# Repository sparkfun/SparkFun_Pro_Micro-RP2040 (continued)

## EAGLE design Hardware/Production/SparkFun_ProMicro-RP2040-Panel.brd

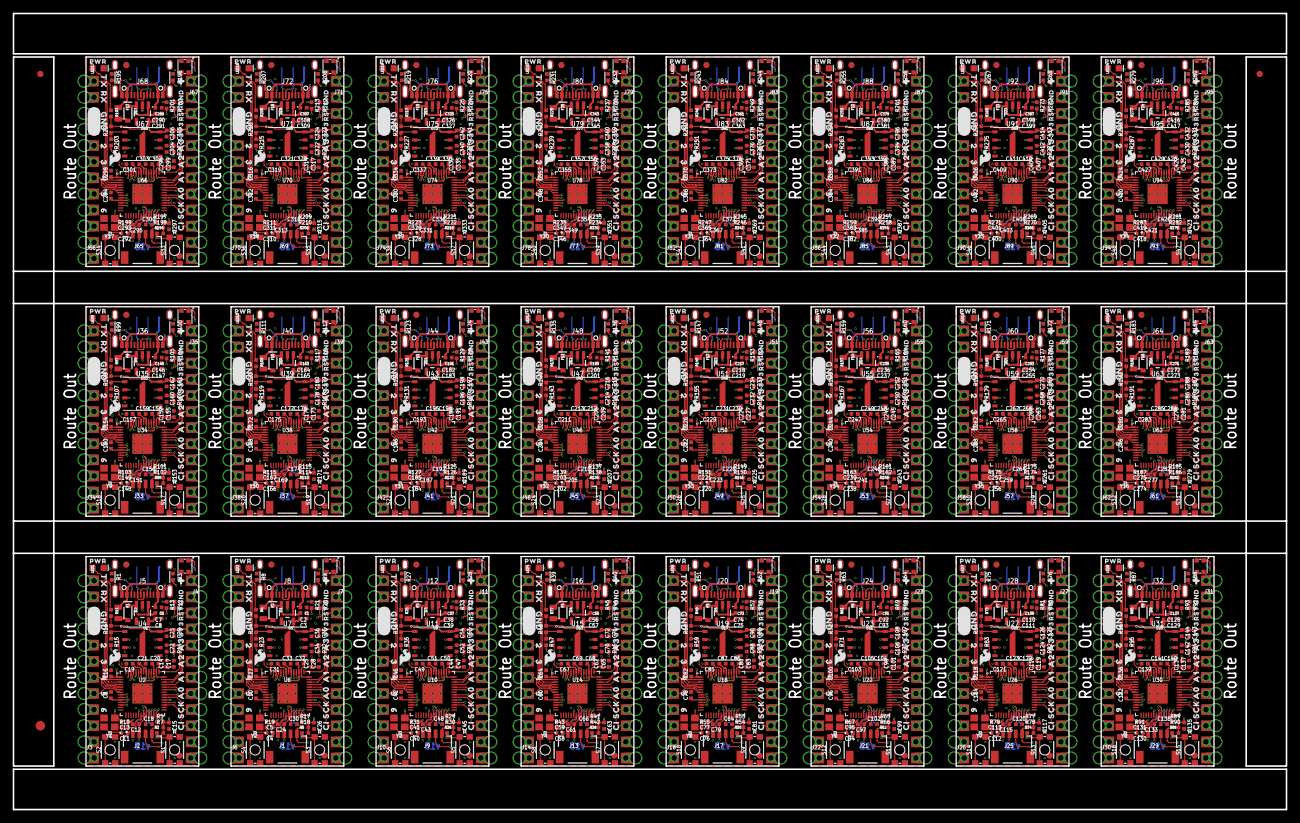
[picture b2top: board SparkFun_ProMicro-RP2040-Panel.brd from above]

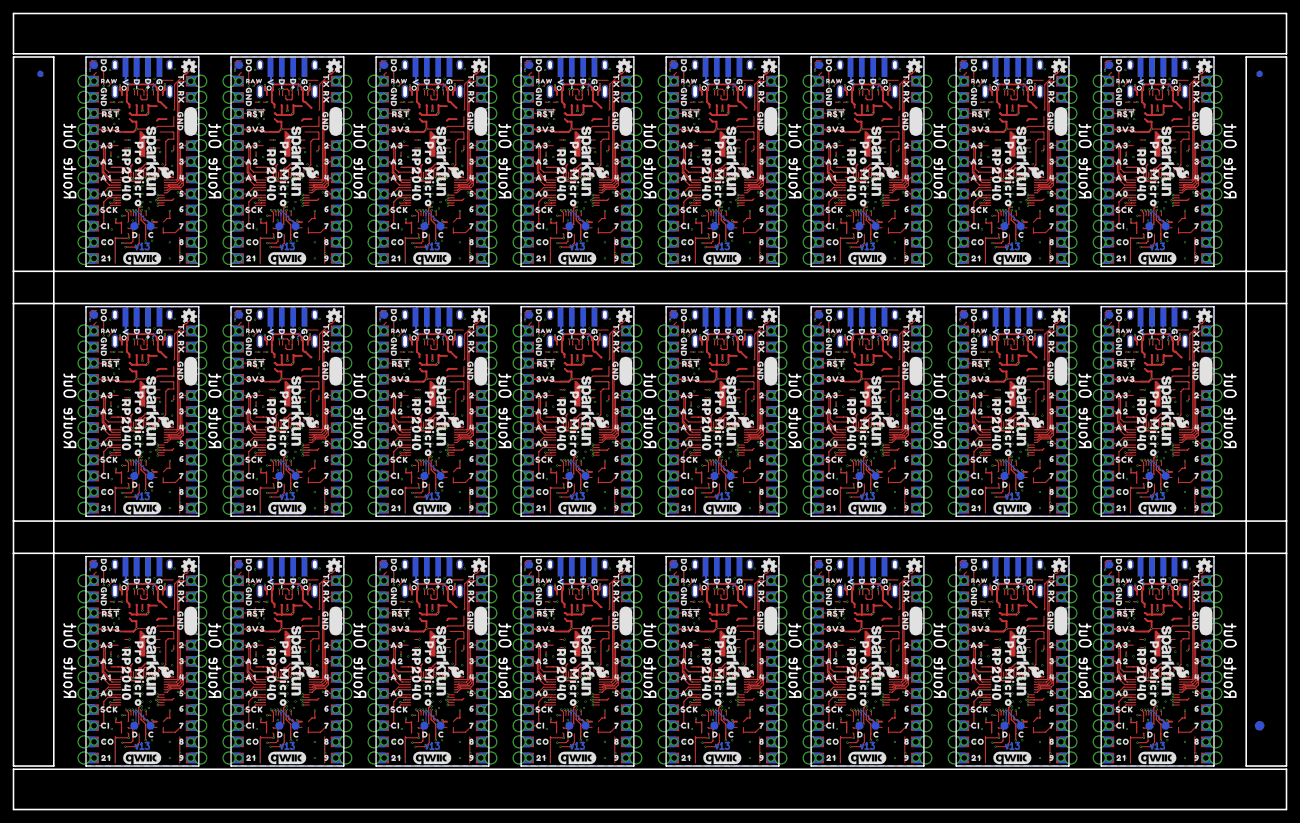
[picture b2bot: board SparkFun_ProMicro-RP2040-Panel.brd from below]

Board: 4 copper layers, 200.7 x 111.8 mm, 2574 parts (939 on the bottom side), 1176 nets.

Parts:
C1, C6, C37, C55, C73, C91, C109, C127, C145, C163, C181, C199, C217, C235, C253, C271, C289, C307, C325, C343, C361, C379, C397, C415: 1.0uF; 0402-TIGHT
C2, C3, C7, C8, C38, C39, C56, C57, C74, C75, C92, C93, C110, C111, C128, C129, C146, C147, C164, C165, C182, C183, C200, C201, C218, C219, C236, C237, C254, C255, C272, C273, C290, C291, C308, C309, C326, C327, C344, C345, C362, C363, C380, C381, C398, C399, C416, C417: 10uF; 0402-TIGHT
C4, C5, C11, C13, C40, C41, C58, C59, C76, C77, C94, C95, C112, C113, C130, C131, C148, C149, C166, C167, C184, C185, C202, C203, C220, C221, C238, C239, C256, C257, C274, C275, C292, C293, C310, C311, C328, C329, C346, C347, C364, C365, C382, C383, C400, C401, C418, C419: 15pF; 0402-TIGHT
C9, C10, C12, C14, C15, C16, C17, C18, C19, C24, C25, C26, C27, C28, C29, C30, C31, C35, C42, C43, C44, C45, C46, C47, C48, C49, C53, C60, C61, C62, C63, C64, C65, C66, C67, C71, C78, C79, C80, C81, C82, C83, C84, C85, C89, C96, C97, C98, C99, C100, C101, C102, C103, C107, C114, C115, C116, C117, C118, C119, C120, C121, C125, C132, C133, C134, C135, C136, C137, C138, C139, C143, C150, C151, C152, C153, C154, C155, C156, C157, C161, C168, C169, C170, C171, C172, C173, C174, C175, C179, C186, C187, C188, C189, C190, C191, C192, C193, C197, C204, C205, C206, C207, C208, C209, C210, C211, C215, C222, C223, C224, C225, C226, C227, C228, C229, C233, C240, C241, C242, C243, C244, C245, C246, C247, C251, C258, C259, C260, C261, C262, C263, C264, C265, C269, C276, C277, C278, C279, C280, C281, C282, C283, C287, C294, C295, C296, C297, C298, C299, C300, C301, C305, C312, C313, C314, C315, C316, C317, C318, C319, C323, C330, C331, C332, C333, C334, C335, C336, C337, C341, C348, C349, C350, C351, C352, C353, C354, C355, C359, C366, C367, C368, C369, C370, C371, C372, C373, C377, C384, C385, C386, C387, C388, C389, C390, C391, C395, C402, C403, C404, C405, C406, C407, C408, C409, C413, C420, C421, C422, C423, C424, C425, C426, C427, C431: 0.1uF; 0402-TIGHT
C20, C21, C22, C23, C32, C33, C34, C36, C50, C51, C52, C54, C68, C69, C70, C72, C86, C87, C88, C90, C104, C105, C106, C108, C122, C123, C124, C126, C140, C141, C142, C144, C158, C159, C160, C162, C176, C177, C178, C180, C194, C195, C196, C198, C212, C213, C214, C216, C230, C231, C232, C234, C248, C249, C250, C252, C266, C267, C268, C270, C284, C285, C286, C288, C302, C303, C304, C306, C320, C321, C322, C324, C338, C339, C340, C342, C356, C357, C358, C360, C374, C375, C376, C378, C392, C393, C394, C396, C410, C411, C412, C414, C428, C429, C430, C432: 2.2uF; 0402-TIGHT
D1, D2, D3, D4, D5, D6, D7, D8, D9, D10, D11, D12, D13, D14, D15, D16, D17, D18, D19, D20, D21, D22, D23, D24: 3A/10V/280mV; SOD-323
E$1, E$2, E$3, E$4: FIDUCIAL-1X2
E$5, E$6: FIDUCIAL-1.5X3
F1, F2, F3, F4, F5, F6, F7, F8, F9, F10, F11, F12, F13, F14, F15, F16, F17, F18, F19, F20, F21, F22, F23, F24: 6V 0.5A; 0805
J1, J2, J9, J13, J17, J21, J25, J29, J33, J37, J41, J45, J49, J53, J57, J61, J65, J69, J73, J77, J81, J85, J89, J93: Qwiic; JST04_1MM_RA
J3, J4, J6, J7, J10, J11, J14, J15, J18, J19, J22, J23, J26, J27, J30, J31, J34, J35, J38, J39, J42, J43, J46, J47, J50, J51, J54, J55, J58, J59, J62, J63, J66, J67, J70, J71, J74, J75, J78, J79, J82, J83, J86, J87, J90, J91, J94, J95: 1X12_CASTELLATED
J5, J8, J12, J16, J20, J24, J28, J32, J36, J40, J44, J48, J52, J56, J60, J64, J68, J72, J76, J80, J84, J88, J92, J96: USB Female Type C Connector; USB-C-16P_4LAYER-PADS
JP1, JP2, JP3, JP4, JP6, JP7, JP9, JP10, JP12, JP13, JP16, JP17, JP19, JP20, JP22, JP23, JP25, JP26, JP28, JP29, JP31, JP32, JP34, JP35, JP37, JP38, JP40, JP41, JP43, JP44, JP46, JP47, JP49, JP50, JP52, JP53, JP55, JP56, JP58, JP59, JP61, JP62, JP64, JP65, JP67, JP68, JP70, JP71: FIDUCIAL1X2; FIDUCIAL-1X2
JP5, JP8, JP11, JP14, JP15, JP18, JP21, JP24, JP27, JP30, JP33, JP36, JP39, JP42, JP45, JP48, JP51, JP54, JP57, JP60, JP63, JP66, JP69, JP72: USB_SOLDER_PADS; USB-SOLDER-PADS
LED1, LED2, LED3, LED4, LED5, LED6, LED7, LED8, LED9, LED10, LED11, LED12, LED13, LED14, LED15, LED16, LED17, LED18, LED19, LED20, LED21, LED22, LED23, LED24: RED; LED-0603
LOGO1, LOGO2, LOGO7, LOGO10, LOGO13, LOGO16, LOGO19, LOGO22, LOGO25, LOGO28, LOGO31, LOGO34, LOGO37, LOGO40, LOGO43, LOGO46, LOGO49, LOGO52, LOGO55, LOGO58, LOGO61, LOGO64, LOGO67, LOGO70: SFE_LOGO_NAME_FLAME.1_INCH; SFE_LOGO_NAME_FLAME_.1
LOGO3, LOGO5, LOGO8, LOGO11, LOGO14, LOGO17, LOGO20, LOGO23, LOGO26, LOGO29, LOGO32, LOGO35, LOGO38, LOGO41, LOGO44, LOGO47, LOGO50, LOGO53, LOGO56, LOGO59, LOGO62, LOGO65, LOGO68, LOGO71: QWIIC_LOGO_6MM; QWIIC_6MM
LOGO4, LOGO6, LOGO9, LOGO12, LOGO15, LOGO18, LOGO21, LOGO24, LOGO27, LOGO30, LOGO33, LOGO36, LOGO39, LOGO42, LOGO45, LOGO48, LOGO51, LOGO54, LOGO57, LOGO60, LOGO63, LOGO66, LOGO69, LOGO72: SFE_LOGO_FLAME.1_INCH; SFE_LOGO_FLAME_.1
R1, R3, R8, R9, R27, R28, R39, R40, R51, R52, R63, R64, R75, R76, R87, R88, R99, R100, R111, R112, R123, R124, R135, R136, R147, R148, R159, R160, R171, R172, R183, R184, R195, R196, R207, R208, R219, R220, R231, R232, R243, R244, R255, R256, R267, R268, R279, R280: 5.1k; 0402-TIGHT
R2, R6, R16, R24, R26, R36, R38, R48, R50, R60, R62, R72, R74, R84, R86, R96, R98, R108, R110, R120, R122, R132, R134, R144, R146, R156, R158, R168, R170, R180, R182, R192, R194, R204, R206, R216, R218, R228, R230, R240, R242, R252, R254, R264, R266, R276, R278, R288: 10k; 0402-TIGHT
R4, R10, R11, R15, R19, R23, R25, R31, R35, R37, R43, R47, R49, R55, R59, R61, R67, R71, R73, R79, R83, R85, R91, R95, R97, R103, R107, R109, R115, R119, R121, R127, R131, R133, R139, R143, R145, R151, R155, R157, R163, R167, R169, R175, R179, R181, R187, R191, R193, R199, R203, R205, R211, R215, R217, R223, R227, R229, R235, R239, R241, R247, R251, R253, R259, R263, R265, R271, R275, R277, R283, R287: 1k; 0402-TIGHT
R5, R7, R17, R18, R29, R30, R41, R42, R53, R54, R65, R66, R77, R78, R89, R90, R101, R102, R113, R114, R125, R126, R137, R138, R149, R150, R161, R162, R173, R174, R185, R186, R197, R198, R209, R210, R221, R222, R233, R234, R245, R246, R257, R258, R269, R270, R281, R282: 2.2k; 0402-TIGHT
R12, R13, R20, R21, R32, R33, R44, R45, R56, R57, R68, R69, R80, R81, R92, R93, R104, R105, R116, R117, R128, R129, R140, R141, R152, R153, R164, R165, R176, R177, R188, R189, R200, R201, R212, R213, R224, R225, R236, R237, R248, R249, R260, R261, R272, R273, R284, R285: 27; 0402-TIGHT
R14, R22, R34, R46, R58, R70, R82, R94, R106, R118, R130, R142, R154, R166, R178, R190, R202, R214, R226, R238, R250, R262, R274, R286: 200; 0402-TIGHT
S1, S3, S5, S7, S9, S11, S13, S15, S17, S19, S21, S23, S25, S27, S29, S31, S33, S35, S37, S39, S41, S43, S45, S47: Reset; TACTILE_SWITCH_SMD_4.6X2.8MM
S2, S4, S6, S8, S10, S12, S14, S16, S18, S20, S22, S24, S26, S28, S30, S32, S34, S36, S38, S40, S42, S44, S46, S48: Boot; TACTILE_SWITCH_SMD_4.6X2.8MM
TP1, TP2, TP3, TP4, TP5, TP6, TP7, TP8, TP9, TP10, TP11, TP12, TP13, TP14, TP15, TP16, TP17, TP18, TP19, TP20, TP21, TP22, TP23, TP24, TP25, TP26, TP27, TP28, TP29, TP30, TP31, TP32, TP33, TP34, TP35, TP36, TP37, TP38, TP39, TP40, TP41, TP42, TP43, TP44, TP45, TP46, TP47, TP48, TP49, TP50, TP51, TP52, TP53, TP54, TP55, TP56, TP57, TP58, TP59, TP60, TP61, TP62, TP63, TP64, TP65, TP66, TP67, TP68, TP69, TP70, TP71, TP72: PAD.03X.05
U1, U5, U9, U13, U17, U21, U25, U29, U33, U37, U41, U45, U49, U53, U57, U61, U65, U69, U73, U77, U81, U85, U89, U93: 3.3V; SOT23-5
U2, U6, U10, U14, U18, U22, U26, U30, U34, U38, U42, U46, U50, U54, U58, U62, U66, U70, U74, U78, U82, U86, U90, U94: RP2040; QFN-56
U3, U8, U12, U16, U20, U24, U28, U32, U36, U40, U44, U48, U52, U56, U60, U64, U68, U72, U76, U80, U84, U88, U92, U96: WS2812-2020
U4, U7, U11, U15, U19, U23, U27, U31, U35, U39, U43, U47, U51, U55, U59, U63, U67, U71, U75, U79, U83, U87, U91, U95: W25QXX128MBIT; WSON-8-6X5-SKINNY_CENTERPAD
U$1, U$11, U$42, U$80, U$110, U$134, U$164, U$188, U$218, U$242, U$272, U$296, U$326, U$350, U$380, U$404, U$434, U$458, U$488, U$512, U$542, U$566, U$596, U$620, U$650, U$674, U$704, U$728, U$758, U$782, U$812, U$836, U$866, U$890, U$920, U$944, U$974, U$998, U$1028, U$1052, U$1082, U$1106, U$1136, U$1160, U$1190, U$1214, U$1244, U$1268: A00
U$2, U$70, U$128, U$182, U$236, U$290, U$344, U$398, U$452, U$506, U$560, U$614, U$668, U$722, U$776, U$830, U$884, U$938, U$992, U$1046, U$1100, U$1154, U$1208, U$1262: GND_0
U$3, U$41, U$109, U$163, U$217, U$271, U$325, U$379, U$433, U$487, U$541, U$595, U$649, U$703, U$757, U$811, U$865, U$919, U$973, U$1027, U$1081, U$1135, U$1189, U$1243: OSHW-LOGOMINI; OSHW-LOGO-MINI
U$4, U$104, U$158, U$212, U$266, U$320, U$374, U$428, U$482, U$536, U$590, U$644, U$698, U$752, U$806, U$860, U$914, U$968, U$1022, U$1076, U$1130, U$1184, U$1238, U$1292: PRO_MICRO0
U$5, U$103, U$157, U$211, U$265, U$319, U$373, U$427, U$481, U$535, U$589, U$643, U$697, U$751, U$805, U$859, U$913, U$967, U$1021, U$1075, U$1129, U$1183, U$1237, U$1291: #0
U$6, U$71, U$129, U$183, U$237, U$291, U$345, U$399, U$453, U$507, U$561, U$615, U$669, U$723, U$777, U$831, U$885, U$939, U$993, U$1047, U$1101, U$1155, U$1209, U$1263: 70
U$7, U$72, U$130, U$184, U$238, U$292, U$346, U$400, U$454, U$508, U$562, U$616, U$670, U$724, U$778, U$832, U$886, U$940, U$994, U$1048, U$1102, U$1156, U$1210, U$1264: 81
U$8, U$77, U$131, U$185, U$239, U$293, U$347, U$401, U$455, U$509, U$563, U$617, U$671, U$725, U$779, U$833, U$887, U$941, U$995, U$1049, U$1103, U$1157, U$1211, U$1265: 92
U$9, U$46, U$64, U$78, U$114, U$132, U$168, U$186, U$222, U$240, U$276, U$294, U$330, U$348, U$384, U$402, U$438, U$456, U$492, U$510, U$546, U$564, U$600, U$618, U$654, U$672, U$708, U$726, U$762, U$780, U$816, U$834, U$870, U$888, U$924, U$942, U$978, U$996, U$1032, U$1050, U$1086, U$1104, U$1140, U$1158, U$1194, U$1212, U$1248, U$1266: CI4
U$10, U$48, U$67, U$79, U$116, U$133, U$170, U$187, U$224, U$241, U$278, U$295, U$332, U$349, U$386, U$403, U$440, U$457, U$494, U$511, U$548, U$565, U$602, U$619, U$656, U$673, U$710, U$727, U$764, U$781, U$818, U$835, U$872, U$889, U$926, U$943, U$980, U$997, U$1034, U$1051, U$1088, U$1105, U$1142, U$1159, U$1196, U$1213, U$1250, U$1267: SCK3
U$12, U$20, U$43, U$81, U$111, U$135, U$165, U$189, U$219, U$243, U$273, U$297, U$327, U$351, U$381, U$405, U$435, U$459, U$489, U$513, U$543, U$567, U$597, U$621, U$651, U$675, U$705, U$729, U$759, U$783, U$813, U$837, U$867, U$891, U$921, U$945, U$975, U$999, U$1029, U$1053, U$1083, U$1107, U$1137, U$1161, U$1191, U$1215, U$1245, U$1269: A10
U$13, U$33, U$44, U$82, U$112, U$136, U$166, U$190, U$220, U$244, U$274, U$298, U$328, U$352, U$382, U$406, U$436, U$460, U$490, U$514, U$544, U$568, U$598, U$622, U$652, U$676, U$706, U$730, U$760, U$784, U$814, U$838, U$868, U$892, U$922, U$946, U$976, U$1000, U$1030, U$1054, U$1084, U$1108, U$1138, U$1162, U$1192, U$1216, U$1246, U$1270: A21
U$14, U$39, U$45, U$83, U$113, U$137, U$167, U$191, U$221, U$245, U$275, U$299, U$329, U$353, U$383, U$407, U$437, U$461, U$491, U$515, U$545, U$569, U$599, U$623, U$653, U$677, U$707, U$731, U$761, U$785, U$815, U$839, U$869, U$893, U$923, U$947, U$977, U$1001, U$1031, U$1055, U$1085, U$1109, U$1139, U$1163, U$1193, U$1217, U$1247, U$1271: A32
U$15, U$22, U$62, U$74, U$86, U$99, U$125, U$140, U$153, U$179, U$194, U$207, U$233, U$248, U$261, U$287, U$302, U$315, U$341, U$356, U$369, U$395, U$410, U$423, U$449, U$464, U$477, U$503, U$518, U$531, U$557, U$572, U$585, U$611, U$626, U$639, U$665, U$680, U$693, U$719, U$734, U$747, U$773, U$788, U$801, U$827, U$842, U$855, U$881, U$896, U$909, U$935, U$950, U$963, U$989, U$1004, U$1017, U$1043, U$1058, U$1071, U$1097, U$1112, U$1125, U$1151, U$1166, U$1179, U$1205, U$1220, U$1233, U$1259, U$1274, U$1287: GND2
U$16, U$98, U$152, U$206, U$260, U$314, U$368, U$422, U$476, U$530, U$584, U$638, U$692, U$746, U$800, U$854, U$908, U$962, U$1016, U$1070, U$1124, U$1178, U$1232, U$1286: 3V3_0
U$17, U$100, U$154, U$208, U$262, U$316, U$370, U$424, U$478, U$532, U$586, U$640, U$694, U$748, U$802, U$856, U$910, U$964, U$1018, U$1072, U$1126, U$1180, U$1234, U$1288: RAW0
U$18, U$106, U$160, U$214, U$268, U$322, U$376, U$430, U$484, U$538, U$592, U$646, U$700, U$754, U$808, U$862, U$916, U$970, U$1024, U$1078, U$1132, U$1186, U$1240, U$1294: C0
U$19, U$65, U$76, U$84, U$127, U$138, U$181, U$192, U$235, U$246, U$289, U$300, U$343, U$354, U$397, U$408, U$451, U$462, U$505, U$516, U$559, U$570, U$613, U$624, U$667, U$678, U$721, U$732, U$775, U$786, U$829, U$840, U$883, U$894, U$937, U$948, U$991, U$1002, U$1045, U$1056, U$1099, U$1110, U$1153, U$1164, U$1207, U$1218, U$1261, U$1272: TX0
U$21, U$63, U$75, U$85, U$126, U$139, U$180, U$193, U$234, U$247, U$288, U$301, U$342, U$355, U$396, U$409, U$450, U$463, U$504, U$517, U$558, U$571, U$612, U$625, U$666, U$679, U$720, U$733, U$774, U$787, U$828, U$841, U$882, U$895, U$936, U$949, U$990, U$1003, U$1044, U$1057, U$1098, U$1111, U$1152, U$1165, U$1206, U$1219, U$1260, U$1273: RX1
U$23, U$49, U$53, U$87, U$117, U$141, U$171, U$195, U$225, U$249, U$279, U$303, U$333, U$357, U$387, U$411, U$441, U$465, U$495, U$519, U$549, U$573, U$603, U$627, U$657, U$681, U$711, U$735, U$765, U$789, U$819, U$843, U$873, U$897, U$927, U$951, U$981, U$1005, U$1035, U$1059, U$1089, U$1113, U$1143, U$1167, U$1197, U$1221, U$1251, U$1275: 20
U$24, U$50, U$54, U$88, U$118, U$142, U$172, U$196, U$226, U$250, U$280, U$304, U$334, U$358, U$388, U$412, U$442, U$466, U$496, U$520, U$550, U$574, U$604, U$628, U$658, U$682, U$712, U$736, U$766, U$790, U$820, U$844, U$874, U$898, U$928, U$952, U$982, U$1006, U$1036, U$1060, U$1090, U$1114, U$1144, U$1168, U$1198, U$1222, U$1252, U$1276: 31
U$25, U$51, U$55, U$89, U$119, U$143, U$173, U$197, U$227, U$251, U$281, U$305, U$335, U$359, U$389, U$413, U$443, U$467, U$497, U$521, U$551, U$575, U$605, U$629, U$659, U$683, U$713, U$737, U$767, U$791, U$821, U$845, U$875, U$899, U$929, U$953, U$983, U$1007, U$1037, U$1061, U$1091, U$1115, U$1145, U$1169, U$1199, U$1223, U$1253, U$1277: 42
U$26, U$52, U$56, U$90, U$120, U$144, U$174, U$198, U$228, U$252, U$282, U$306, U$336, U$360, U$390, U$414, U$444, U$468, U$498, U$522, U$552, U$576, U$606, U$630, U$660, U$684, U$714, U$738, U$768, U$792, U$822, U$846, U$876, U$900, U$930, U$954, U$984, U$1008, U$1038, U$1062, U$1092, U$1116, U$1146, U$1170, U$1200, U$1224, U$1254, U$1278: 53
U$27, U$57, U$58, U$91, U$121, U$145, U$175, U$199, U$229, U$253, U$283, U$307, U$337, U$361, U$391, U$415, U$445, U$469, U$499, U$523, U$553, U$577, U$607, U$631, U$661, U$685, U$715, U$739, U$769, U$793, U$823, U$847, U$877, U$901, U$931, U$955, U$985, U$1009, U$1039, U$1063, U$1093, U$1117, U$1147, U$1171, U$1201, U$1225, U$1255, U$1279: 64
U$28, U$92, U$146, U$200, U$254, U$308, U$362, U$416, U$470, U$524, U$578, U$632, U$686, U$740, U$794, U$848, U$902, U$956, U$1010, U$1064, U$1118, U$1172, U$1226, U$1280: D#1
U$29, U$93, U$147, U$201, U$255, U$309, U$363, U$417, U$471, U$525, U$579, U$633, U$687, U$741, U$795, U$849, U$903, U$957, U$1011, U$1065, U$1119, U$1173, U$1227, U$1281: D#2
U$30, U$94, U$148, U$202, U$256, U$310, U$364, U$418, U$472, U$526, U$580, U$634, U$688, U$742, U$796, U$850, U$904, U$958, U$1012, U$1066, U$1120, U$1174, U$1228, U$1282: G0
U$31, U$95, U$149, U$203, U$257, U$311, U$365, U$419, U$473, U$527, U$581, U$635, U$689, U$743, U$797, U$851, U$905, U$959, U$1013, U$1067, U$1121, U$1175, U$1229, U$1283: V3
U$32, U$96, U$150, U$204, U$258, U$312, U$366, U$420, U$474, U$528, U$582, U$636, U$690, U$744, U$798, U$852, U$906, U$960, U$1014, U$1068, U$1122, U$1176, U$1230, U$1284: 210
U$34, U$97, U$151, U$205, U$259, U$313, U$367, U$421, U$475, U$529, U$583, U$637, U$691, U$745, U$799, U$853, U$907, U$961, U$1015, U$1069, U$1123, U$1177, U$1231, U$1285: #RST#0
U$35, U$107, U$161, U$215, U$269, U$323, U$377, U$431, U$485, U$539, U$593, U$647, U$701, U$755, U$809, U$863, U$917, U$971, U$1025, U$1079, U$1133, U$1187, U$1241, U$1295: D1
U$36, U$101, U$155, U$209, U$263, U$317, U$371, U$425, U$479, U$533, U$587, U$641, U$695, U$749, U$803, U$857, U$911, U$965, U$1019, U$1073, U$1127, U$1181, U$1235, U$1289: B0
U$37, U$102, U$156, U$210, U$264, U$318, U$372, U$426, U$480, U$534, U$588, U$642, U$696, U$750, U$804, U$858, U$912, U$966, U$1020, U$1074, U$1128, U$1182, U$1236, U$1290: R0
U$38, U$105, U$159, U$213, U$267, U$321, U$375, U$429, U$483, U$537, U$591, U$645, U$699, U$753, U$807, U$861, U$915, U$969, U$1023, U$1077, U$1131, U$1185, U$1239, U$1293: RP20401
U$40, U$108, U$162, U$216, U$270, U$324, U$378, U$432, U$486, U$540, U$594, U$648, U$702, U$756, U$810, U$864, U$918, U$972, U$1026, U$1080, U$1134, U$1188, U$1242, U$1296: DO0
U$47, U$66, U$115, U$169, U$223, U$277, U$331, U$385, U$439, U$493, U$547, U$601, U$655, U$709, U$763, U$817, U$871, U$925, U$979, U$1033, U$1087, U$1141, U$1195, U$1249: CO5
U$59, U$68, U$122, U$176, U$230, U$284, U$338, U$392, U$446, U$500, U$554, U$608, U$662, U$716, U$770, U$824, U$878, U$932, U$986, U$1040, U$1094, U$1148, U$1202, U$1256: #RST#1
U$60, U$69, U$123, U$177, U$231, U$285, U$339, U$393, U$447, U$501, U$555, U$609, U$663, U$717, U$771, U$825, U$879, U$933, U$987, U$1041, U$1095, U$1149, U$1203, U$1257: 3V30
U$61, U$73, U$124, U$178, U$232, U$286, U$340, U$394, U$448, U$502, U$556, U$610, U$664, U$718, U$772, U$826, U$880, U$934, U$988, U$1042, U$1096, U$1150, U$1204, U$1258: PWR0
Y1, Y2, Y3, Y4, Y5, Y6, Y7, Y8, Y9, Y10, Y11, Y12, Y13, Y14, Y15, Y16, Y17, Y18, Y19, Y20, Y21, Y22, Y23, Y24: 12MHz; CRYSTAL-SMD-2X2.5MM

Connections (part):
0/TX0: J3.12, J3.12B, U2.2
0/TX1: J6.12, J6.12B, U6.2
0/TX2: J10.12, J10.12B, U10.2
0/TX3: J14.12, J14.12B, U14.2
0/TX4: J18.12, J18.12B, U18.2
0/TX5: J22.12, J22.12B, U22.2
0/TX6: J26.12, J26.12B, U26.2
0/TX7: J30.12, J30.12B, U30.2
0/TX8: J34.12, J34.12B, U34.2
0/TX9: J38.12, J38.12B, U38.2
0/TX10: J42.12, J42.12B, U42.2
0/TX11: J46.12, J46.12B, U46.2
0/TX12: J50.12, J50.12B, U50.2
0/TX13: J54.12, J54.12B, U54.2
0/TX14: J58.12, J58.12B, U58.2
0/TX15: J62.12, J62.12B, U62.2
0/TX16: J66.12, J66.12B, U66.2
0/TX17: J70.12, J70.12B, U70.2
0/TX18: J74.12, J74.12B, U74.2
0/TX19: J78.12, J78.12B, U78.2
0/TX20: J82.12, J82.12B, U82.2
0/TX21: J86.12, J86.12B, U86.2
0/TX22: J90.12, J90.12B, U90.2
0/TX23: J94.12, J94.12B, U94.2
1: J6.5, J6.5B, U6.7
1.1V: C18.1, C19.1, C20.1, U2.23, U2.45, U2.50
1.1V1: C30.1, C31.1, C32.1, U6.23, U6.45, U6.50
1.1V2: C48.1, C49.1, C50.1, U10.23, U10.45, U10.50
1.1V3: C66.1, C67.1, C68.1, U14.23, U14.45, U14.50
1.1V4: C84.1, C85.1, C86.1, U18.23, U18.45, U18.50
1.1V5: C102.1, C103.1, C104.1, U22.23, U22.45, U22.50
1.1V6: C120.1, C121.1, C122.1, U26.23, U26.45, U26.50
1.1V7: C138.1, C139.1, C140.1, U30.23, U30.45, U30.50
1.1V8: C156.1, C157.1, C158.1, U34.23, U34.45, U34.50
1.1V9: C174.1, C175.1, C176.1, U38.23, U38.45, U38.50
1.1V10: C192.1, C193.1, C194.1, U42.23, U42.45, U42.50
1.1V11: C210.1, C211.1, C212.1, U46.23, U46.45, U46.50
1.1V12: C228.1, C229.1, C230.1, U50.23, U50.45, U50.50
1.1V13: C246.1, C247.1, C248.1, U54.23, U54.45, U54.50
1.1V14: C264.1, C265.1, C266.1, U58.23, U58.45, U58.50
1.1V15: C282.1, C283.1, C284.1, U62.23, U62.45, U62.50
1.1V16: C300.1, C301.1, C302.1, U66.23, U66.45, U66.50
1.1V17: C318.1, C319.1, C320.1, U70.23, U70.45, U70.50
1.1V18: C336.1, C337.1, C338.1, U74.23, U74.45, U74.50
1.1V19: C354.1, C355.1, C356.1, U78.23, U78.45, U78.50
1.1V20: C372.1, C373.1, C374.1, U82.23, U82.45, U82.50
1.1V21: C390.1, C391.1, C392.1, U86.23, U86.45, U86.50
1.1V22: C408.1, C409.1, C410.1, U90.23, U90.45, U90.50
1.1V23: C426.1, C427.1, C428.1, U94.23, U94.45, U94.50
1/RX0: J3.11, J3.11B, U2.3
1/RX1: J6.11, J6.11B, U6.3
1/RX2: J10.11, J10.11B, U10.3
1/RX3: J14.11, J14.11B, U14.3
1/RX4: J18.11, J18.11B, U18.3
1/RX5: J22.11, J22.11B, U22.3
1/RX6: J26.11, J26.11B, U26.3
1/RX7: J30.11, J30.11B, U30.3
1/RX8: J34.11, J34.11B, U34.3
1/RX9: J38.11, J38.11B, U38.3
1/RX10: J42.11, J42.11B, U42.3
1/RX11: J46.11, J46.11B, U46.3
1/RX12: J50.11, J50.11B, U50.3
1/RX13: J54.11, J54.11B, U54.3
1/RX14: J58.11, J58.11B, U58.3
1/RX15: J62.11, J62.11B, U62.3
1/RX16: J66.11, J66.11B, U66.3
1/RX17: J70.11, J70.11B, U70.3
1/RX18: J74.11, J74.11B, U74.3
1/RX19: J78.11, J78.11B, U78.3
1/RX20: J82.11, J82.11B, U82.3
1/RX21: J86.11, J86.11B, U86.3
1/RX22: J90.11, J90.11B, U90.3
1/RX23: J94.11, J94.11B, U94.3
2: J3.8, J3.8B, U2.4
3: J3.7, J3.7B, U2.5
3.3V: C8.2, C9.1, C12.1, C14.1, C15.1, C16.1, C17.1, C21.1, C23.1, C29.1, J2.2, J4.4, J4.4B, R2.2, R5.2, R7.2, R11.2, R14.2, R16.2, U1.5, U2.1, U2.10, U2.22, U2.33, U2.42, U2.44, U2.48, U2.49, U4.8
3.3V1: C3.2, C10.1, C24.1, C25.1, C26.1, C27.1, C28.1, C33.1, C35.1, C36.1, J1.2, J7.4, J7.4B, R4.2, R6.2, R17.2, R18.2, R22.2, R24.2, U5.5, U6.1, U6.10, U6.22, U6.33, U6.42, U6.44, U6.48, U6.49, U7.8
3.3V2: C39.2, C42.1, C43.1, C44.1, C45.1, C46.1, C47.1, C51.1, C53.1, C54.1, J9.2, J11.4, J11.4B, R25.2, R26.2, R29.2, R30.2, R34.2, R36.2, U9.5, U10.1, U10.10, U10.22, U10.33, U10.42, U10.44, U10.48, U10.49, U11.8
3.3V3: C57.2, C60.1, C61.1, C62.1, C63.1, C64.1, C65.1, C69.1, C71.1, C72.1, J13.2, J15.4, J15.4B, R37.2, R38.2, R41.2, R42.2, R46.2, R48.2, U13.5, U14.1, U14.10, U14.22, U14.33, U14.42, U14.44, U14.48, U14.49, U15.8
3.3V4: C75.2, C78.1, C79.1, C80.1, C81.1, C82.1, C83.1, C87.1, C89.1, C90.1, J17.2, J19.4, J19.4B, R49.2, R50.2, R53.2, R54.2, R58.2, R60.2, U17.5, U18.1, U18.10, U18.22, U18.33, U18.42, U18.44, U18.48, U18.49, U19.8
3.3V5: C93.2, C96.1, C97.1, C98.1, C99.1, C100.1, C101.1, C105.1, C107.1, C108.1, J21.2, J23.4, J23.4B, R61.2, R62.2, R65.2, R66.2, R70.2, R72.2, U21.5, U22.1, U22.10, U22.22, U22.33, U22.42, U22.44, U22.48, U22.49, U23.8
3.3V6: C111.2, C114.1, C115.1, C116.1, C117.1, C118.1, C119.1, C123.1, C125.1, C126.1, J25.2, J27.4, J27.4B, R73.2, R74.2, R77.2, R78.2, R82.2, R84.2, U25.5, U26.1, U26.10, U26.22, U26.33, U26.42, U26.44, U26.48, U26.49, U27.8
3.3V7: C129.2, C132.1, C133.1, C134.1, C135.1, C136.1, C137.1, C141.1, C143.1, C144.1, J29.2, J31.4, J31.4B, R85.2, R86.2, R89.2, R90.2, R94.2, R96.2, U29.5, U30.1, U30.10, U30.22, U30.33, U30.42, U30.44, U30.48, U30.49, U31.8
3.3V8: C147.2, C150.1, C151.1, C152.1, C153.1, C154.1, C155.1, C159.1, C161.1, C162.1, J33.2, J35.4, J35.4B, R97.2, R98.2, R101.2, R102.2, R106.2, R108.2, U33.5, U34.1, U34.10, U34.22, U34.33, U34.42, U34.44, U34.48, U34.49, U35.8
3.3V9: C165.2, C168.1, C169.1, C170.1, C171.1, C172.1, C173.1, C177.1, C179.1, C180.1, J37.2, J39.4, J39.4B, R109.2, R110.2, R113.2, R114.2, R118.2, R120.2, U37.5, U38.1, U38.10, U38.22, U38.33, U38.42, U38.44, U38.48, U38.49, U39.8
3.3V10: C183.2, C186.1, C187.1, C188.1, C189.1, C190.1, C191.1, C195.1, C197.1, C198.1, J41.2, J43.4, J43.4B, R121.2, R122.2, R125.2, R126.2, R130.2, R132.2, U41.5, U42.1, U42.10, U42.22, U42.33, U42.42, U42.44, U42.48, U42.49, U43.8
3.3V11: C201.2, C204.1, C205.1, C206.1, C207.1, C208.1, C209.1, C213.1, C215.1, C216.1, J45.2, J47.4, J47.4B, R133.2, R134.2, R137.2, R138.2, R142.2, R144.2, U45.5, U46.1, U46.10, U46.22, U46.33, U46.42, U46.44, U46.48, U46.49, U47.8
3.3V12: C219.2, C222.1, C223.1, C224.1, C225.1, C226.1, C227.1, C231.1, C233.1, C234.1, J49.2, J51.4, J51.4B, R145.2, R146.2, R149.2, R150.2, R154.2, R156.2, U49.5, U50.1, U50.10, U50.22, U50.33, U50.42, U50.44, U50.48, U50.49, U51.8
3.3V13: C237.2, C240.1, C241.1, C242.1, C243.1, C244.1, C245.1, C249.1, C251.1, C252.1, J53.2, J55.4, J55.4B, R157.2, R158.2, R161.2, R162.2, R166.2, R168.2, U53.5, U54.1, U54.10, U54.22, U54.33, U54.42, U54.44, U54.48, U54.49, U55.8
3.3V14: C255.2, C258.1, C259.1, C260.1, C261.1, C262.1, C263.1, C267.1, C269.1, C270.1, J57.2, J59.4, J59.4B, R169.2, R170.2, R173.2, R174.2, R178.2, R180.2, U57.5, U58.1, U58.10, U58.22, U58.33, U58.42, U58.44, U58.48, U58.49, U59.8
3.3V15: C273.2, C276.1, C277.1, C278.1, C279.1, C280.1, C281.1, C285.1, C287.1, C288.1, J61.2, J63.4, J63.4B, R181.2, R182.2, R185.2, R186.2, R190.2, R192.2, U61.5, U62.1, U62.10, U62.22, U62.33, U62.42, U62.44, U62.48, U62.49, U63.8
3.3V16: C291.2, C294.1, C295.1, C296.1, C297.1, C298.1, C299.1, C303.1, C305.1, C306.1, J65.2, J67.4, J67.4B, R193.2, R194.2, R197.2, R198.2, R202.2, R204.2, U65.5, U66.1, U66.10, U66.22, U66.33, U66.42, U66.44, U66.48, U66.49, U67.8
3.3V17: C309.2, C312.1, C313.1, C314.1, C315.1, C316.1, C317.1, C321.1, C323.1, C324.1, J69.2, J71.4, J71.4B, R205.2, R206.2, R209.2, R210.2, R214.2, R216.2, U69.5, U70.1, U70.10, U70.22, U70.33, U70.42, U70.44, U70.48, U70.49, U71.8
3.3V18: C327.2, C330.1, C331.1, C332.1, C333.1, C334.1, C335.1, C339.1, C341.1, C342.1, J73.2, J75.4, J75.4B, R217.2, R218.2, R221.2, R222.2, R226.2, R228.2, U73.5, U74.1, U74.10, U74.22, U74.33, U74.42, U74.44, U74.48, U74.49, U75.8
3.3V19: C345.2, C348.1, C349.1, C350.1, C351.1, C352.1, C353.1, C357.1, C359.1, C360.1, J77.2, J79.4, J79.4B, R229.2, R230.2, R233.2, R234.2, R238.2, R240.2, U77.5, U78.1, U78.10, U78.22, U78.33, U78.42, U78.44, U78.48, U78.49, U79.8
3.3V20: C363.2, C366.1, C367.1, C368.1, C369.1, C370.1, C371.1, C375.1, C377.1, C378.1, J81.2, J83.4, J83.4B, R241.2, R242.2, R245.2, R246.2, R250.2, R252.2, U81.5, U82.1, U82.10, U82.22, U82.33, U82.42, U82.44, U82.48, U82.49, U83.8
3.3V21: C381.2, C384.1, C385.1, C386.1, C387.1, C388.1, C389.1, C393.1, C395.1, C396.1, J85.2, J87.4, J87.4B, R253.2, R254.2, R257.2, R258.2, R262.2, R264.2, U85.5, U86.1, U86.10, U86.22, U86.33, U86.42, U86.44, U86.48, U86.49, U87.8
3.3V22: C399.2, C402.1, C403.1, C404.1, C405.1, C406.1, C407.1, C411.1, C413.1, C414.1, J89.2, J91.4, J91.4B, R265.2, R266.2, R269.2, R270.2, R274.2, R276.2, U89.5, U90.1, U90.10, U90.22, U90.33, U90.42, U90.44, U90.48, U90.49, U91.8
3.3V23: C417.2, C420.1, C421.1, C422.1, C423.1, C424.1, C425.1, C429.1, C431.1, C432.1, J93.2, J95.4, J95.4B, R277.2, R278.2, R281.2, R282.2, R286.2, R288.2, U93.5, U94.1, U94.10, U94.22, U94.33, U94.42, U94.44, U94.48, U94.49, U95.8
4: J3.6, J3.6B, U2.6
5: J3.5, J3.5B, U2.7
6: J3.4, J3.4B, U2.8
7: J3.3, J3.3B, U2.9
8: J6.6, J6.6B, U6.6
8/TX1: J3.2, J3.2B, U2.11
8/TX2: J6.2, J6.2B, U6.11
8/TX3: J10.2, J10.2B, U10.11
8/TX4: J14.2, J14.2B, U14.11
8/TX5: J18.2, J18.2B, U18.11
8/TX6: J22.2, J22.2B, U22.11
8/TX7: J26.2, J26.2B, U26.11
8/TX8: J30.2, J30.2B, U30.11
8/TX9: J34.2, J34.2B, U34.11
8/TX10: J38.2, J38.2B, U38.11
8/TX11: J42.2, J42.2B, U42.11
8/TX12: J46.2, J46.2B, U46.11
8/TX13: J50.2, J50.2B, U50.11
8/TX14: J54.2, J54.2B, U54.11
8/TX15: J58.2, J58.2B, U58.11
8/TX16: J62.2, J62.2B, U62.11
8/TX17: J66.2, J66.2B, U66.11
8/TX18: J70.2, J70.2B, U70.11
8/TX19: J74.2, J74.2B, U74.11
8/TX20: J78.2, J78.2B, U78.11
8/TX21: J82.2, J82.2B, U82.11
8/TX22: J86.2, J86.2B, U86.11
8/TX23: J90.2, J90.2B, U90.11
8/TX24: J94.2, J94.2B, U94.11
9: J6.4, J6.4B, U6.8
9/RX1: J3.1, J3.1B, U2.12
9/RX2: J6.1, J6.1B, U6.12
9/RX3: J10.1, J10.1B, U10.12
9/RX4: J14.1, J14.1B, U14.12
9/RX5: J18.1, J18.1B, U18.12
9/RX6: J22.1, J22.1B, U22.12
9/RX7: J26.1, J26.1B, U26.12
9/RX8: J30.1, J30.1B, U30.12
9/RX9: J34.1, J34.1B, U34.12
9/RX10: J38.1, J38.1B, U38.12
9/RX11: J42.1, J42.1B, U42.12
9/RX12: J46.1, J46.1B, U46.12
9/RX13: J50.1, J50.1B, U50.12
9/RX14: J54.1, J54.1B, U54.12
9/RX15: J58.1, J58.1B, U58.12
9/RX16: J62.1, J62.1B, U62.12
9/RX17: J66.1, J66.1B, U66.12
9/RX18: J70.1, J70.1B, U70.12
9/RX19: J74.1, J74.1B, U74.12
9/RX20: J78.1, J78.1B, U78.12
9/RX21: J82.1, J82.1B, U82.12
9/RX22: J86.1, J86.1B, U86.12
9/RX23: J90.1, J90.1B, U90.12
9/RX24: J94.1, J94.1B, U94.12
10: J6.3, J6.3B, U6.9
11: J6.8, J6.8B, U6.4
12: J6.7, J6.7B, U6.5
13: J10.5, J10.5B, U10.7
14: J10.6, J10.6B, U10.6
15: J10.4, J10.4B, U10.8
16: J10.3, J10.3B, U10.9
16/SDA: J2.3, R5.1, U2.27
16/SDA1: J1.3, R17.1, U6.27
16/SDA2: J9.3, R29.1, U10.27
16/SDA3: J13.3, R41.1, U14.27
16/SDA4: J17.3, R53.1, U18.27
16/SDA5: J21.3, R65.1, U22.27
16/SDA6: J25.3, R77.1, U26.27
16/SDA7: J29.3, R89.1, U30.27
16/SDA8: J33.3, R101.1, U34.27
16/SDA9: J37.3, R113.1, U38.27
16/SDA10: J41.3, R125.1, U42.27
16/SDA11: J45.3, R137.1, U46.27
16/SDA12: J49.3, R149.1, U50.27
16/SDA13: J53.3, R161.1, U54.27
16/SDA14: J57.3, R173.1, U58.27
16/SDA15: J61.3, R185.1, U62.27
16/SDA16: J65.3, R197.1, U66.27
16/SDA17: J69.3, R209.1, U70.27
16/SDA18: J73.3, R221.1, U74.27
16/SDA19: J77.3, R233.1, U78.27
16/SDA20: J81.3, R245.1, U82.27
16/SDA21: J85.3, R257.1, U86.27
16/SDA22: J89.3, R269.1, U90.27
16/SDA23: J93.3, R281.1, U94.27
17: J10.8, J10.8B, U10.4
17/SCL: J2.4, R7.1, U2.28
17/SCL1: J1.4, R18.1, U6.28
17/SCL2: J9.4, R30.1, U10.28
17/SCL3: J13.4, R42.1, U14.28
17/SCL4: J17.4, R54.1, U18.28
17/SCL5: J21.4, R66.1, U22.28
17/SCL6: J25.4, R78.1, U26.28
17/SCL7: J29.4, R90.1, U30.28
17/SCL8: J33.4, R102.1, U34.28
17/SCL9: J37.4, R114.1, U38.28
17/SCL10: J41.4, R126.1, U42.28
17/SCL11: J45.4, R138.1, U46.28
17/SCL12: J49.4, R150.1, U50.28
17/SCL13: J53.4, R162.1, U54.28
17/SCL14: J57.4, R174.1, U58.28
17/SCL15: J61.4, R186.1, U62.28
17/SCL16: J65.4, R198.1, U66.28
17/SCL17: J69.4, R210.1, U70.28
17/SCL18: J73.4, R222.1, U74.28
17/SCL19: J77.4, R234.1, U78.28
17/SCL20: J81.4, R246.1, U82.28
17/SCL21: J85.4, R258.1, U86.28
17/SCL22: J89.4, R270.1, U90.28
17/SCL23: J93.4, R282.1, U94.28
18: J10.7, J10.7B, U10.5
19: J14.5, J14.5B, U14.7
20: J14.6, J14.6B, U14.6
20/SPI_CIPO: J4.10, J4.10B, U2.31
20/SPI_CIPO1: J7.10, J7.10B, U6.31
20/SPI_CIPO2: J11.10, J11.10B, U10.31
20/SPI_CIPO3: J15.10, J15.10B, U14.31
20/SPI_CIPO4: J19.10, J19.10B, U18.31
20/SPI_CIPO5: J23.10, J23.10B, U22.31
20/SPI_CIPO6: J27.10, J27.10B, U26.31
20/SPI_CIPO7: J31.10, J31.10B, U30.31
20/SPI_CIPO8: J35.10, J35.10B, U34.31
20/SPI_CIPO9: J39.10, J39.10B, U38.31
20/SPI_CIPO10: J43.10, J43.10B, U42.31
20/SPI_CIPO11: J47.10, J47.10B, U46.31
20/SPI_CIPO12: J51.10, J51.10B, U50.31
20/SPI_CIPO13: J55.10, J55.10B, U54.31
20/SPI_CIPO14: J59.10, J59.10B, U58.31
20/SPI_CIPO15: J63.10, J63.10B, U62.31
20/SPI_CIPO16: J67.10, J67.10B, U66.31
20/SPI_CIPO17: J71.10, J71.10B, U70.31
20/SPI_CIPO18: J75.10, J75.10B, U74.31
20/SPI_CIPO19: J79.10, J79.10B, U78.31
20/SPI_CIPO20: J83.10, J83.10B, U82.31
20/SPI_CIPO21: J87.10, J87.10B, U86.31
20/SPI_CIPO22: J91.10, J91.10B, U90.31
20/SPI_CIPO23: J95.10, J95.10B, U94.31
21: J14.4, J14.4B, U14.8
21/SPI_!CS!: J4.12, J4.12B, U2.32
21/SPI_!CS!1: J7.12, J7.12B, U6.32
21/SPI_!CS!2: J11.12, J11.12B, U10.32
21/SPI_!CS!3: J15.12, J15.12B, U14.32
21/SPI_!CS!4: J19.12, J19.12B, U18.32
21/SPI_!CS!5: J23.12, J23.12B, U22.32
21/SPI_!CS!6: J27.12, J27.12B, U26.32
21/SPI_!CS!7: J31.12, J31.12B, U30.32
21/SPI_!CS!8: J35.12, J35.12B, U34.32
21/SPI_!CS!9: J39.12, J39.12B, U38.32
21/SPI_!CS!10: J43.12, J43.12B, U42.32
21/SPI_!CS!11: J47.12, J47.12B, U46.32
21/SPI_!CS!12: J51.12, J51.12B, U50.32
21/SPI_!CS!13: J55.12, J55.12B, U54.32
21/SPI_!CS!14: J59.12, J59.12B, U58.32
21/SPI_!CS!15: J63.12, J63.12B, U62.32
21/SPI_!CS!16: J67.12, J67.12B, U66.32
21/SPI_!CS!17: J71.12, J71.12B, U70.32
21/SPI_!CS!18: J75.12, J75.12B, U74.32
21/SPI_!CS!19: J79.12, J79.12B, U78.32
21/SPI_!CS!20: J83.12, J83.12B, U82.32
21/SPI_!CS!21: J87.12, J87.12B, U86.32
21/SPI_!CS!22: J91.12, J91.12B, U90.32
21/SPI_!CS!23: J95.12, J95.12B, U94.32
22: J14.3, J14.3B, U14.9
22/SPI_SCK: J4.9, J4.9B, U2.34
22/SPI_SCK1: J7.9, J7.9B, U6.34
22/SPI_SCK2: J11.9, J11.9B, U10.34
22/SPI_SCK3: J15.9, J15.9B, U14.34
22/SPI_SCK4: J19.9, J19.9B, U18.34
22/SPI_SCK5: J23.9, J23.9B, U22.34
22/SPI_SCK6: J27.9, J27.9B, U26.34
22/SPI_SCK7: J31.9, J31.9B, U30.34
22/SPI_SCK8: J35.9, J35.9B, U34.34
22/SPI_SCK9: J39.9, J39.9B, U38.34
22/SPI_SCK10: J43.9, J43.9B, U42.34
22/SPI_SCK11: J47.9, J47.9B, U46.34
22/SPI_SCK12: J51.9, J51.9B, U50.34
22/SPI_SCK13: J55.9, J55.9B, U54.34
22/SPI_SCK14: J59.9, J59.9B, U58.34
22/SPI_SCK15: J63.9, J63.9B, U62.34
22/SPI_SCK16: J67.9, J67.9B, U66.34
22/SPI_SCK17: J71.9, J71.9B, U70.34
22/SPI_SCK18: J75.9, J75.9B, U74.34
22/SPI_SCK19: J79.9, J79.9B, U78.34
22/SPI_SCK20: J83.9, J83.9B, U82.34
22/SPI_SCK21: J87.9, J87.9B, U86.34
22/SPI_SCK22: J91.9, J91.9B, U90.34
22/SPI_SCK23: J95.9, J95.9B, U94.34
23: J14.8, J14.8B, U14.4
23/SPI_COPI: J4.11, J4.11B, U2.35
23/SPI_COPI1: J7.11, J7.11B, U6.35
23/SPI_COPI2: J11.11, J11.11B, U10.35
23/SPI_COPI3: J15.11, J15.11B, U14.35
23/SPI_COPI4: J19.11, J19.11B, U18.35
23/SPI_COPI5: J23.11, J23.11B, U22.35
23/SPI_COPI6: J27.11, J27.11B, U26.35
23/SPI_COPI7: J31.11, J31.11B, U30.35
23/SPI_COPI8: J35.11, J35.11B, U34.35
23/SPI_COPI9: J39.11, J39.11B, U38.35
23/SPI_COPI10: J43.11, J43.11B, U42.35
23/SPI_COPI11: J47.11, J47.11B, U46.35
23/SPI_COPI12: J51.11, J51.11B, U50.35
23/SPI_COPI13: J55.11, J55.11B, U54.35
23/SPI_COPI14: J59.11, J59.11B, U58.35
23/SPI_COPI15: J63.11, J63.11B, U62.35
23/SPI_COPI16: J67.11, J67.11B, U66.35
23/SPI_COPI17: J71.11, J71.11B, U70.35
23/SPI_COPI18: J75.11, J75.11B, U74.35
23/SPI_COPI19: J79.11, J79.11B, U78.35
23/SPI_COPI20: J83.11, J83.11B, U82.35
23/SPI_COPI21: J87.11, J87.11B, U86.35
23/SPI_COPI22: J91.11, J91.11B, U90.35
23/SPI_COPI23: J95.11, J95.11B, U94.35
24: J14.7, J14.7B, U14.5
25: J18.5, J18.5B, U18.7
25/WS2812-DI: U2.37, U3.3
25/WS2812-DI1: U6.37, U8.3
25/WS2812-DI2: U10.37, U12.3
25/WS2812-DI3: U14.37, U16.3
25/WS2812-DI4: U18.37, U20.3
25/WS2812-DI5: U22.37, U24.3
25/WS2812-DI6: U26.37, U28.3
25/WS2812-DI7: U30.37, U32.3
25/WS2812-DI8: U34.37, U36.3
25/WS2812-DI9: U38.37, U40.3
25/WS2812-DI10: U42.37, U44.3
25/WS2812-DI11: U46.37, U48.3
25/WS2812-DI12: U50.37, U52.3
25/WS2812-DI13: U54.37, U56.3
25/WS2812-DI14: U58.37, U60.3
25/WS2812-DI15: U62.37, U64.3
25/WS2812-DI16: U66.37, U68.3
25/WS2812-DI17: U70.37, U72.3
25/WS2812-DI18: U74.37, U76.3
25/WS2812-DI19: U78.37, U80.3
25/WS2812-DI20: U82.37, U84.3
25/WS2812-DI21: U86.37, U88.3
25/WS2812-DI22: U90.37, U92.3
25/WS2812-DI23: U94.37, U96.3
26: J18.6, J18.6B, U18.6
27: J18.4, J18.4B, U18.8
28: J18.3, J18.3B, U18.9
29: J18.8, J18.8B, U18.4
30: J18.7, J18.7B, U18.5
31: J22.5, J22.5B, U22.7
32: J22.6, J22.6B, U22.6
33: J22.4, J22.4B, U22.8
34: J22.3, J22.3B, U22.9
35: J22.8, J22.8B, U22.4
36: J22.7, J22.7B, U22.5
37: J26.5, J26.5B, U26.7
38: J26.6, J26.6B, U26.6
39: J26.4, J26.4B, U26.8
40: J26.3, J26.3B, U26.9
41: J26.8, J26.8B, U26.4
42: J26.7, J26.7B, U26.5
43: J30.5, J30.5B, U30.7
44: J30.6, J30.6B, U30.6
45: J30.4, J30.4B, U30.8
46: J30.3, J30.3B, U30.9
47: J30.8, J30.8B, U30.4
48: J30.7, J30.7B, U30.5
49: J34.5, J34.5B, U34.7
50: J34.6, J34.6B, U34.6
51: J34.4, J34.4B, U34.8
52: J34.3, J34.3B, U34.9
53: J34.8, J34.8B, U34.4
54: J34.7, J34.7B, U34.5
55: J38.5, J38.5B, U38.7
56: J38.6, J38.6B, U38.6
57: J38.4, J38.4B, U38.8
58: J38.3, J38.3B, U38.9
59: J38.8, J38.8B, U38.4
60: J38.7, J38.7B, U38.5
61: J42.5, J42.5B, U42.7
62: J42.6, J42.6B, U42.6
63: J42.4, J42.4B, U42.8
64: J42.3, J42.3B, U42.9
65: J42.8, J42.8B, U42.4
66: J42.7, J42.7B, U42.5
67: J46.5, J46.5B, U46.7
68: J46.6, J46.6B, U46.6
69: J46.4, J46.4B, U46.8
70: J46.3, J46.3B, U46.9
71: J46.8, J46.8B, U46.4
72: J46.7, J46.7B, U46.5
73: J50.5, J50.5B, U50.7
74: J50.6, J50.6B, U50.6
75: J50.4, J50.4B, U50.8
76: J50.3, J50.3B, U50.9
77: J50.8, J50.8B, U50.4
78: J50.7, J50.7B, U50.5
79: J54.5, J54.5B, U54.7
80: J54.6, J54.6B, U54.6
81: J54.4, J54.4B, U54.8
82: J54.3, J54.3B, U54.9
83: J54.8, J54.8B, U54.4
84: J54.7, J54.7B, U54.5
85: J58.5, J58.5B, U58.7
86: J58.6, J58.6B, U58.6
87: J58.4, J58.4B, U58.8
88: J58.3, J58.3B, U58.9
89: J58.8, J58.8B, U58.4
90: J58.7, J58.7B, U58.5
91: J62.5, J62.5B, U62.7
92: J62.6, J62.6B, U62.6
93: J62.4, J62.4B, U62.8
94: J62.3, J62.3B, U62.9
95: J62.8, J62.8B, U62.4
96: J62.7, J62.7B, U62.5
97: J66.5, J66.5B, U66.7
98: J66.6, J66.6B, U66.6
99: J66.4, J66.4B, U66.8
100: J66.3, J66.3B, U66.9
101: J66.8, J66.8B, U66.4
102: J66.7, J66.7B, U66.5
103: J70.5, J70.5B, U70.7
104: J70.6, J70.6B, U70.6
105: J70.4, J70.4B, U70.8
106: J70.3, J70.3B, U70.9
107: J70.8, J70.8B, U70.4
108: J70.7, J70.7B, U70.5
109: J74.5, J74.5B, U74.7
110: J74.6, J74.6B, U74.6
111: J74.4, J74.4B, U74.8
112: J74.3, J74.3B, U74.9
113: J74.8, J74.8B, U74.4
114: J74.7, J74.7B, U74.5
115: J78.5, J78.5B, U78.7
116: J78.6, J78.6B, U78.6
117: J78.4, J78.4B, U78.8
118: J78.3, J78.3B, U78.9
119: J78.8, J78.8B, U78.4
120: J78.7, J78.7B, U78.5
121: J82.5, J82.5B, U82.7
122: J82.6, J82.6B, U82.6
123: J82.4, J82.4B, U82.8
124: J82.3, J82.3B, U82.9
125: J82.8, J82.8B, U82.4
126: J82.7, J82.7B, U82.5
127: J86.5, J86.5B, U86.7
128: J86.6, J86.6B, U86.6
129: J86.4, J86.4B, U86.8
130: J86.3, J86.3B, U86.9
131: J86.8, J86.8B, U86.4
132: J86.7, J86.7B, U86.5
133: J90.5, J90.5B, U90.7
134: J90.6, J90.6B, U90.6
135: J90.4, J90.4B, U90.8
136: J90.3, J90.3B, U90.9
137: J90.8, J90.8B, U90.4
138: J90.7, J90.7B, U90.5
139: J94.5, J94.5B, U94.7
140: J94.6, J94.6B, U94.6
141: J94.4, J94.4B, U94.8
142: J94.3, J94.3B, U94.9
143: J94.8, J94.8B, U94.4
144: J94.7, J94.7B, U94.5
!RESET!: J4.3, J4.3B, R2.1, S1.3, S1.4, U2.26
!RESET!1: J7.3, J7.3B, R6.1, S3.3, S3.4, U6.26
!RESET!2: J11.3, J11.3B, R26.1, S5.3, S5.4, U10.26
!RESET!3: J15.3, J15.3B, R38.1, S7.3, S7.4, U14.26
!RESET!4: J19.3, J19.3B, R50.1, S9.3, S9.4, U18.26
!RESET!5: J23.3, J23.3B, R62.1, S11.3, S11.4, U22.26
!RESET!6: J27.3, J27.3B, R74.1, S13.3, S13.4, U26.26
!RESET!7: J31.3, J31.3B, R86.1, S15.3, S15.4, U30.26
!RESET!8: J35.3, J35.3B, R98.1, S17.3, S17.4, U34.26
!RESET!9: J39.3, J39.3B, R110.1, S19.3, S19.4, U38.26
!RESET!10: J43.3, J43.3B, R122.1, S21.3, S21.4, U42.26
!RESET!11: J47.3, J47.3B, R134.1, S23.3, S23.4, U46.26
!RESET!12: J51.3, J51.3B, R146.1, S25.3, S25.4, U50.26
!RESET!13: J55.3, J55.3B, R158.1, S27.3, S27.4, U54.26
!RESET!14: J59.3, J59.3B, R170.1, S29.3, S29.4, U58.26
!RESET!15: J63.3, J63.3B, R182.1, S31.3, S31.4, U62.26
!RESET!16: J67.3, J67.3B, R194.1, S33.3, S33.4, U66.26
!RESET!17: J71.3, J71.3B, R206.1, S35.3, S35.4, U70.26
!RESET!18: J75.3, J75.3B, R218.1, S37.3, S37.4, U74.26
!RESET!19: J79.3, J79.3B, R230.1, S39.3, S39.4, U78.26
!RESET!20: J83.3, J83.3B, R242.1, S41.3, S41.4, U82.26
!RESET!21: J87.3, J87.3B, R254.1, S43.3, S43.4, U86.26
!RESET!22: J91.3, J91.3B, R266.1, S45.3, S45.4, U90.26
!RESET!23: J95.3, J95.3B, R278.1, S47.3, S47.4, U94.26
A0: J4.8, J4.8B, U2.38
A1: J4.7, J4.7B, U2.39
A2: J4.6, J4.6B, U2.40
A3: J4.5, J4.5B, U2.41
A4: J7.5, J7.5B, U6.41
A5: J7.6, J7.6B, U6.40
A6: J7.7, J7.7B, U6.39
A7: J7.8, J7.8B, U6.38
A8: J11.5, J11.5B, U10.41
A9: J11.6, J11.6B, U10.40
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
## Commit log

2020-12-02 Increase 1.8V trace thickness. Fix reversed 3 silk.
2020-12-02 Cleaning up schematic
2020-12-29 Update silk. Adjust a few 0603 components.
2020-12-29 Silk update
2020-12-29 Flip board to standard view
2020-12-31 Add RAW max voltage warning
2021-01-07 Add DO TP for WS2812
2021-02-10 Update to taller buttons
2021-03-23 Update Eagle File Names to Match Product Name
2021-03-23 Delete rp2040_datasheet.pdf
    Removing outdated datasheet, the latest can be found from Raspberry Pi =)
2021-04-26 Move passives for better DFM
2021-04-27 New panel
2022-01-10 Increase isolation in layers 2/15. Increase to v13.
